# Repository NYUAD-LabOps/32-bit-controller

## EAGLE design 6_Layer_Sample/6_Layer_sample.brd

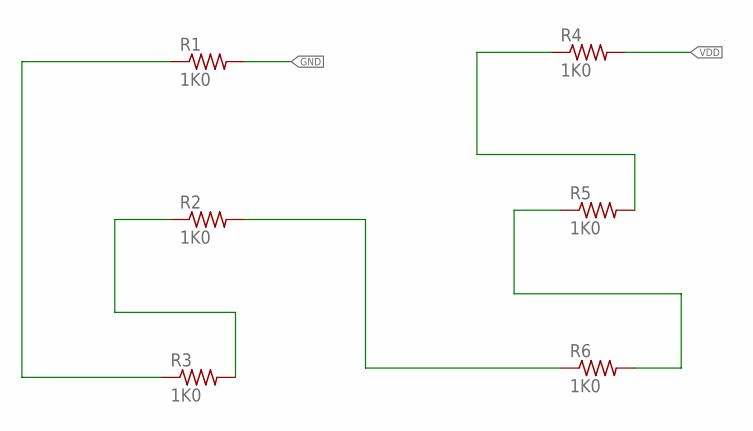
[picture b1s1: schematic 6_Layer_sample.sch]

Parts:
R1, R2, R3, R4, R5, R6: 1K0; 0402

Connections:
GND: R1.P$2 (2)
unnamed: R1.P$1 (1), R3.P$1 (1)
unnamed: R2.P$1 (1), R3.P$2 (2)
unnamed: R2.P$2 (2), R6.P$1 (1)
unnamed: R5.P$1 (1), R6.P$2 (2)
unnamed: R4.P$1 (1), R5.P$2 (2)
VDD: R4.P$2 (2)

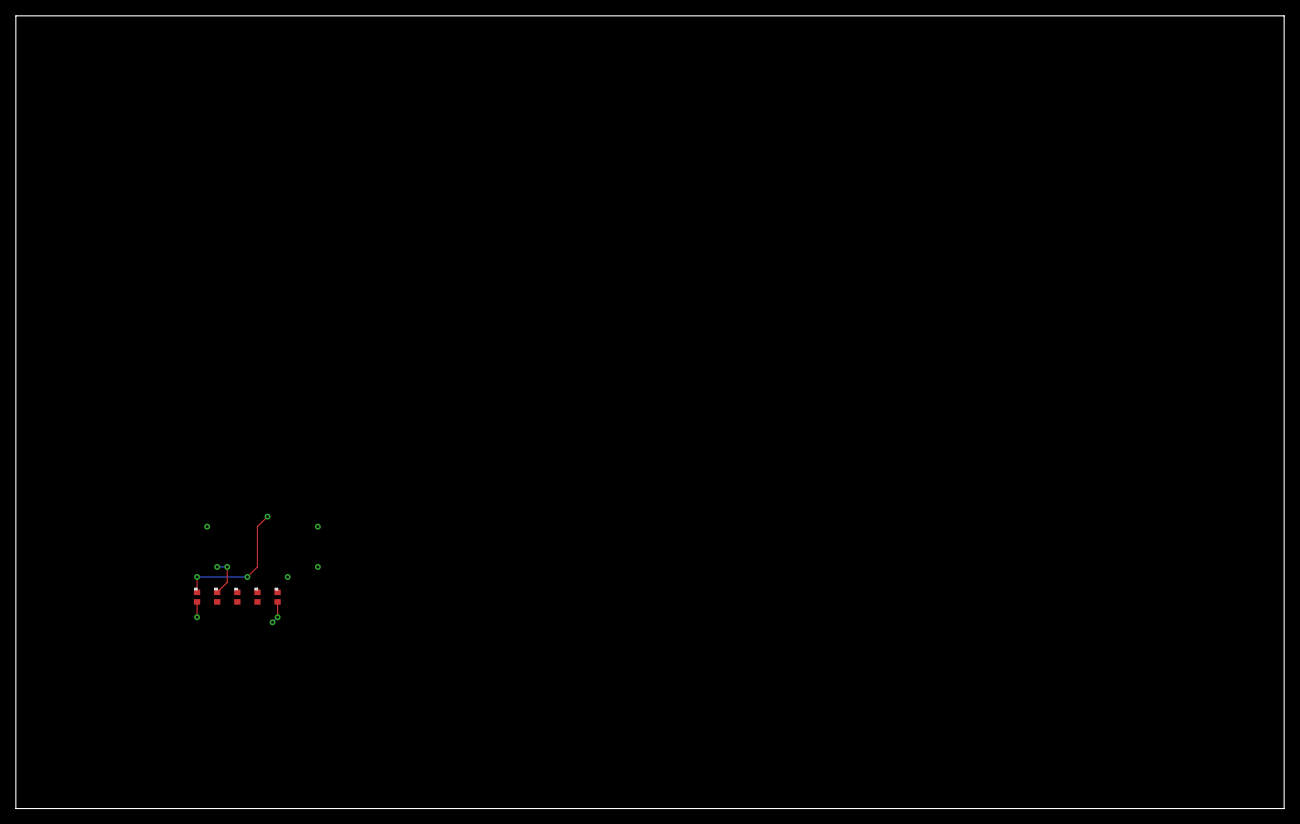
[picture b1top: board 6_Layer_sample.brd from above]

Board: 6 copper layers, 160.0 x 100.0 mm, 6 parts (1 on the bottom side), 5 nets.

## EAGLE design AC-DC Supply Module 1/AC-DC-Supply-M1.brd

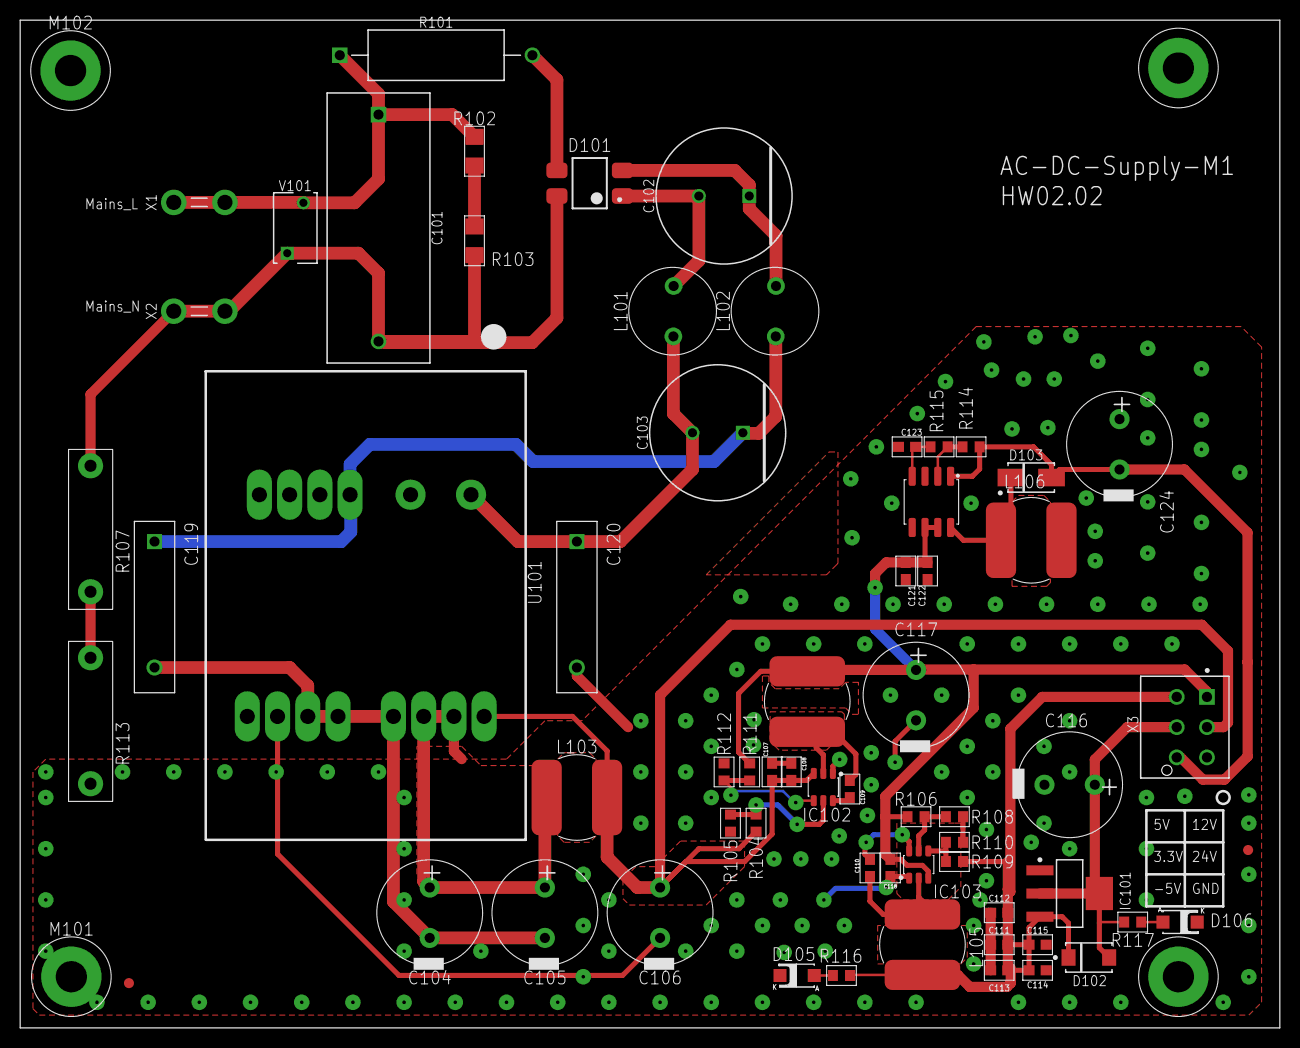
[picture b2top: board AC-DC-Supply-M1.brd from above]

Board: 2 copper layers, 125.0 x 100.0 mm, 67 parts (0 on the bottom side), 29 nets.

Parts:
C101: R49AN347050B1M
C102, C103: 860011378008; RADIAL_D13.0P5.0H25.0
C104, C105, C106, C116, C117, C124: 50PX470MEFC10X20; CAPACITOR-ELKO-RM5-10X16
C107, C109, C110, C115, C123: 100nF/50V; 0603
C108, C118, C121: 1uF/35V; 0603
C111, C112, C113, C114, C122: 10uF/25V; 0603
C119, C120: ERP610W471MEF0; CAP-P12.5-H15-W4-D1
D101: MB10S; SOIC4W
D102: STTH1L06ASTMICROELECTRONICS_STTH1L06A_0_0; SMA_STTH1L06A
D103: SS14; SMA
D105, D106: 26-21/GPC-F3138B/CA; SMD1206-LED
FID101, FID102: FIDUCIAL
IC101: LD1117S33TR; SOT223_LD1117S33TR
IC102, IC103: TPS54202DDCR; SOT23-6
IC104: MAX764CSA+; SOIC8
L101, L102: RLB0914-102KL; THTINDUCTOR8MM7
L103, L104, L105, L106: SRN8040TA-220M
M101, M102, M103, M104: M_HOLE_3M; PCB_SCREW_M3_POWER
R101: ERG-2SJ390V; ERG-2SJ390V_0
R102, R103: R_1206; R1206
R104: 1K 1%; R0603
R105: 10K; R0603
R106: 1K 1 %; R0603
R107, R113: RNF12FTD10M0; RES-RM12.5-VR37
R108, R115: 10k 1%; R0603
R109: 22K 1%; R0603
R110: 3k01 1%; R0603
R111: 100k 1%; R0603
R112: 4.3k 1%; R0603
R114: 33k 1%; R0603
R116: 162R 1%; R0603
R117: 82R 1%; R0603
U101: BPM2417SJ
V101: B72205S0271K101B72205S2131K101; EPCOS_B72205S0271K101_0
X1, X2: 726386-2; TE_726386-2_MODIFIED
X3: MOLEX_206832-0601MOLEX_206832-0601; MOLEX_206832-0601

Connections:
10_AC-DC_SUPPLY:N$1: IC102.4, R111.2, R112.2
10_AC-DC_SUPPLY:N$2: R102.1, R103.2
10_AC-DC_SUPPLY:N$3: R107.2, R113.1
10_AC-DC_SUPPLY:N$4: D101.3, R101.2
10_AC-DC_SUPPLY:N$5: C102.2, D101.1, L101.1
10_AC-DC_SUPPLY:N$6: C102.1, D101.2, L102.1
10_AC-DC_SUPPLY:N$7: C103.2, C120.P$1, L101.2, U101.1
10_AC-DC_SUPPLY:N$8: C103.1, C119.P$1, L102.2, U101.3
10_AC-DC_SUPPLY:N$9: C109.2, IC102.2, L104.1
10_AC-DC_SUPPLY:N$10: IC102.5, R104.1, R105.2
10_AC-DC_SUPPLY:N$11: C104.1, C105.1, L103.1, U101.12, U101.13
10_AC-DC_SUPPLY:N$12: C109.1, IC102.6
10_AC-DC_SUPPLY:N$13: C110.2, IC103.2, L105.1
10_AC-DC_SUPPLY:N$14: IC104.2, R114.1, R115.2
10_AC-DC_SUPPLY:N$15: IC103.4, R109.2, R110.1
10_AC-DC_SUPPLY:N$16: IC103.5, R106.1, R108.2
10_AC-DC_SUPPLY:N$17: D105.1, R116.2
10_AC-DC_SUPPLY:N$18: D103.1, IC104.8, L106.2
10_AC-DC_SUPPLY:N$19: D106.1, R117.2
10_AC-DC_SUPPLY:N$20: C123.1, IC104.4, R115.1
10_AC-DC_SUPPLY:N$21: C110.1, IC103.6
GND: C104.2, C105.2, C106.2, C107.2, C108.2, C111.1, C112.1, C113.1, C114.1, C115.2, C116.2, C117.2, C118.1, C119.P$2, C120.P$2, C121.1, C122.1, C123.2, C124.1, D105.2, D106.2, IC101.1, IC102.1, IC103.1, IC104.3, IC104.5, L106.1, M101.1, M104.1, R105.1, R108.1, R110.2, R112.1, R113.2, U101.08, U101.09, U101.10, U101.11, X3.5
unnamed: C101.1, R101.1, R102.2, V101.2, X1.1, X1.1-2
unnamed: C101.2, D101.4, R103.1, R107.1, V101.1, X2.1, X2.1-2
V_3V3: C116.1, D102.2, IC101.2, IC101.4, R117.1, X3.4
V_5V0: C111.2, C112.2, C113.2, C114.2, C115.1, D102.1, IC101.3, L105.2, R109.1, R116.1, X3.2
V_12V0: C117.1, C118.2, C121.2, C122.2, IC103.3, IC104.6, IC104.7, L104.2, R106.2, R111.1, X3.1
V_24V0: C106.1, C107.1, C108.1, IC102.3, L103.2, R104.2, U101.14, X3.3
V_-5V0: C124.2, D103.2, IC104.1, R114.2, X3.6

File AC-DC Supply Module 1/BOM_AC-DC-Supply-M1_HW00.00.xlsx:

Part | Value | Device | Package | DESCRIPTION | LIB_STATUS | MFN | MFR | OUR-STOCK | OUR_STOCK | PACKAGE2 | PART_VALUE | PRICE-1 | PRICE_1 | STOCK | SUPPLIER-1
C101 | R49AN347050B1M | R49AN347050B1M | R49AN347050B1M | Film,X1,470nF/330Vac,THT | Verified | R49AN347050B1M | Kemet |  | 8 |  | 470nF/330VAC | 1.51 |  |  | Digikey
C102 | 860011378008 | 860011378008 | RADIAL_D13.0P5.0H25.0 | Electrolytic Cap 33µF 400V 13mm Radial WCAP-ATG8 |  |  | 860011378008 |  |  | 4
C103 | 860011378008 | 860011378008 | RADIAL_D13.0P5.0H25.0 | Electrolytic Cap 33µF 400V 13mm Radial WCAP-ATG8 |  |  | 860011378008 |  |  | 4
C104 | 50PX470MEFC10X20 | 50PX470MEFC10X20 | CAPACITOR-ELKO-RM5-10X16 | 470uF ±20% 50V 10mm 20mm 5mm 2000Hrs @ 105℃ -55℃ ~ +105℃ | Prototype | 50PX470MEFC10X20 | Rubicon |  | 20 |  | 470uF/50V | 0.14000000000000001 |  |  | LCSC
C105 | 50PX470MEFC10X20 | 50PX470MEFC10X20 | CAPACITOR-ELKO-RM5-10X16 | 470uF ±20% 50V 10mm 20mm 5mm 2000Hrs @ 105℃ -55℃ ~ +105℃ | Prototype | 50PX470MEFC10X20 | Rubicon |  | 20 |  | 470uF/50V | 0.14000000000000001 |  |  | LCSC
C106 | 50PX470MEFC10X20 | 50PX470MEFC10X20 | CAPACITOR-ELKO-RM5-10X16 | 470uF ±20% 50V 10mm 20mm 5mm 2000Hrs @ 105℃ -55℃ ~ +105℃ | Prototype | 50PX470MEFC10X20 | Rubicon |  | 20 |  | 470uF/50V | 0.14000000000000001 |  |  | LCSC
C107 | 100nF/50V | C_0603 | 603 |  |  | Open Source
C108 | 1uF/35V | C_0603 | 603 |  |  | Open Source
C109 | 100nF/50V | C_0603 | 603 |  |  | Open Source
C110 | 100nF/50V | C_0603 | 603 |  |  | Open Source
C111 | 10uF/25V | C_0603 | 603 |  |  | Open Source
C112 | 10uF/25V | C_0603 | 603 |  |  | Open Source
C113 | 10uF/25V | C_0603 | 603 |  |  | Open Source
C114 | 10uF/25V | C_0603 | 603 |  |  | Open Source
C115 | 100nF/50V | C_0603 | 603 |  |  | Open Source
C116 | 50PX470MEFC10X20 | 50PX470MEFC10X20 | CAPACITOR-ELKO-RM5-10X16 | 470uF ±20% 50V 10mm 20mm 5mm 2000Hrs @ 105℃ -55℃ ~ +105℃ | Prototype | 50PX470MEFC10X20 | Rubicon |  | 20 |  | 470uF/50V | 0.14000000000000001 |  |  | LCSC
C117 | 50PX470MEFC10X20 | 50PX470MEFC10X20 | CAPACITOR-ELKO-RM5-10X16 | 470uF ±20% 50V 10mm 20mm 5mm 2000Hrs @ 105℃ -55℃ ~ +105℃ | Prototype | 50PX470MEFC10X20 | Rubicon |  | 20 |  | 470uF/50V | 0.14000000000000001 |  |  | LCSC
C118 | 1uF/35V | C_0603 | 603 |  |  | Open Source
C119 | ERP610W471MEF0 | ERP610W471MEF0 | CAP-P12.5-H15-W4-D1 | 470 pF ±20% 760VAC Ceramic Capacitor Y5U (E) Radial X1,Y1 | Prototype | ERP610W471MEF0 | Kemet |  | 150 |  | 470pF/760VAC | 0.42 |  |  | Digikey
C120 | ERP610W471MEF0 | ERP610W471MEF0 | CAP-P12.5-H15-W4-D1 | 470 pF ±20% 760VAC Ceramic Capacitor Y5U (E) Radial X1,Y1 | Prototype | ERP610W471MEF0 | Kemet |  | 150 |  | 470pF/760VAC | 0.42 |  |  | Digikey
D101 | MB10S | MB10S | SOIC4W | 0.5 A 1000 V Low Leakage SMT Bridge Rectifier - SOIC-4 | Prototype | MB10S | On Semi, Diodes,MDD |  |  |  | Bridge Rectifier | 0.02 |  | 10 | Digikey
D102 | STTH1L06ASTMICROELECTRONICS_STTH1L06A_0_0 | STTH1L06ASTMICROELECTRONICS_STTH1L06A_0_0 | SMA_STTH1L06A |  |  |  |  |  |  | SMA
D105 | 26-21/GPC-F3138B/CA | 26-21/GPC-F3138B/CA | SMD1206-LED | Green SMD LED 1206, 160mcd | Prototype | 26-21/GPC-F3138B/CA | Everlight |  | 50 |  | Green LED | 0.06 |  |  | LCSC
D106 | 26-21/GPC-F3138B/CA | 26-21/GPC-F3138B/CA | SMD1206-LED | Green SMD LED 1206, 160mcd | Prototype | 26-21/GPC-F3138B/CA | Everlight |  | 50 |  | Green LED | 0.06 |  |  | LCSC
FID101 | FIDUCIAL | FIDUCIAL | FIDUCIAL
FID102 | FIDUCIAL | FIDUCIAL | FIDUCIAL
IC101 | LD1117S33TR | LD1117S33TR | SOT223_LD1117S33TR | LDO,Fixed 15V 3.3V 1.3V @ 800mA SOT-223 | Verified | LD1117S33TR | STmicro, Diodes, TI, |  | 10 |  | xx1117x33xx |  | 7.0000000000000007E-2 |  | LCSC
IC102 | AP63301WU-7 | AP63301WU-7 | SOT23-6 | Buck 3.8V to 32V Input 3A Low IQ Synchronous Buck Converter with Enhanced EMI | Verified |  | Diodes |  | 10 |  | AP63301WU-7 | 0.25 |  |  | Digikey
IC103 | AP63301WU-7 | AP63301WU-7 | SOT23-6 | Buck 3.8V to 32V Input 3A Low IQ Synchronous Buck Converter with Enhanced EMI | Verified |  | Diodes |  | 10 |  | AP63301WU-7 | 0.25 |  |  | Digikey
L101 | RLB0914-102KL | RLB0914-102KL | THTINDUCTOR8MM7 | Inductor Power Wirewound 1mH 10% 252KHz 40Q-Factor Ferrite 300mA 2.1Ohm | Prototype | RLB0914-102KL | Bourns |  | 0 |  | 1mH | 0.42 |  |  | Digikey
L102 | RLB0914-102KL | RLB0914-102KL | THTINDUCTOR8MM7 | Inductor Power Wirewound 1mH 10% 252KHz 40Q-Factor Ferrite 300mA 2.1Ohm | Prototype | RLB0914-102KL | Bourns |  | 0 |  | 1mH | 0.42 |  |  | Digikey
L103 | SRN8040TA-220M | SRN8040TA-220M | SRN8040TA-220M | FIXED IND 22UH 2.9A SMD, 73m-Ohm, Bourns | Verified | SRN8040TA-220M | Bourns |  | 10 |  | 22uH/2.9A |  |  |  | Digikey
L104 | SRN8040TA-220M | SRN8040TA-220M | SRN8040TA-220M | FIXED IND 22UH 2.9A SMD, 73m-Ohm, Bourns | Verified | SRN8040TA-220M | Bourns |  | 10 |  | 22uH/2.9A |  |  |  | Digikey
L105 | SRN8040TA-220M | SRN8040TA-220M | SRN8040TA-220M | FIXED IND 22UH 2.9A SMD, 73m-Ohm, Bourns | Verified | SRN8040TA-220M | Bourns |  | 10 |  | 22uH/2.9A |  |  |  | Digikey
M101 | M_HOLE_3M | M_HOLE_3M | PCB_SCREW_M3_POWER
M102 | M_HOLE_3M | M_HOLE_3M | PCB_SCREW_M3_POWER
M103 | M_HOLE_3M | M_HOLE_3M | PCB_SCREW_M3_POWER
M104 | M_HOLE_3M | M_HOLE_3M | PCB_SCREW_M3_POWER
R101 | ERG-2SJ390V | ERG-2SJ390V | ERG-2SJ390V_0
R102 | R_1206 | R_1206 | R1206 |  | Verified | CRCW1206220KJNEAHP | Vishay |  |  |  | 220K 5%
R103 | R_1206 | R_1206 | R1206 |  | Verified | CRCW1206220KJNEAHP | Vishay |  |  |  | 220K 5%
R104 |  | R_0603 | R0603 |  |  | Open Source
R105 |  | R_0603 | R0603 |  |  | Open Source
R106 |  | R_0603 | R0603 |  |  | Open Source
R107 | RNF12FTD10M0 | RNF12FTD10M0 | RES-RM12.5-VR37 | 10 MOhms ±1% 0.5W, 1/2W Through Hole Resistor Axial Flame Retardant Coating, Sa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 | Prototype | RNF12FTD10M0 | Stackpole Electronics Inc | 20 |  |  | 10Meg 5% | 0.28999999999999998 |  |  | Digikey
R108 |  | R_0603 | R0603 |  |  | Open Source
R109 | 15.8K 1% | R_0603 | R0603 |  |  | Open Source
R110 | 3k01 1% | R_0603 | R0603 |  |  | Open Source
R111 | 47k 1% | R_0603 | R0603 |  |  | Open Source
R112 | 3.3k 1% | R_0603 | R0603 |  |  | Open Source
R113 | RNF12FTD10M0 | RNF12FTD10M0 | RES-RM12.5-VR37 | 10 MOhms ±1% 0.5W, 1/2W Through Hole Resistor Axial Flame Retardant Coating, Sa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 | Prototype | RNF12FTD10M0 | Stackpole Electronics Inc | 20 |  |  | 10Meg 5% | 0.28999999999999998 |  |  | Digikey
R116 | 162R 1% | R_0603 | R0603 |  |  | Open Source
R117 | 82R 1% | R_0603 | R0603 |  |  | Open Source
U101 | BPM2417SJ | BPM2417SJ | BPM2417SJ | Ac/Dc Power Supply Module | Prototype | BPM2417SJ | Tamura |  | 5 |  | Power Sources | 7 |  |  | Digikey
V101 | B72205S0271K101B72205S2131K101 | B72205S0271K101B72205S2131K101 | EPCOS_B72205S0271K101_0 |  | Verified | B72205S0271K1011 | EPCOS |  | 10 |  | 430V, 400A | 0.31 |  |  | Digikey
X1 | 726386-2 | 726386-2 | TE_726386-2_MODIFIED | 0.250 (6.35mm) Quick Connect Male - Solder Connector Non-Insulated" |  | 726386-2 | TE Connectivity |  |  |  | 6.35mmx8mm | 0.24 |  |  | Digikey
X2 | 726386-2 | 726386-2 | TE_726386-2_MODIFIED | 0.250 (6.35mm) Quick Connect Male - Solder Connector Non-Insulated" |  | 726386-2 | TE Connectivity |  |  |  | 6.35mmx8mm | 0.24 |  |  | Digikey
X3 | MOLEX_206832-0601MOLEX_206832-0601 | MOLEX_206832-0601MOLEX_206832-0601 | MOLEX_206832-0601 | Connector Header Through Hole 6 position 3mm Microfit | Prototype | 206832-0601 | Molex |  | 20 |  | 6CCT x 2Row | 1.32 |  |  | Digikey

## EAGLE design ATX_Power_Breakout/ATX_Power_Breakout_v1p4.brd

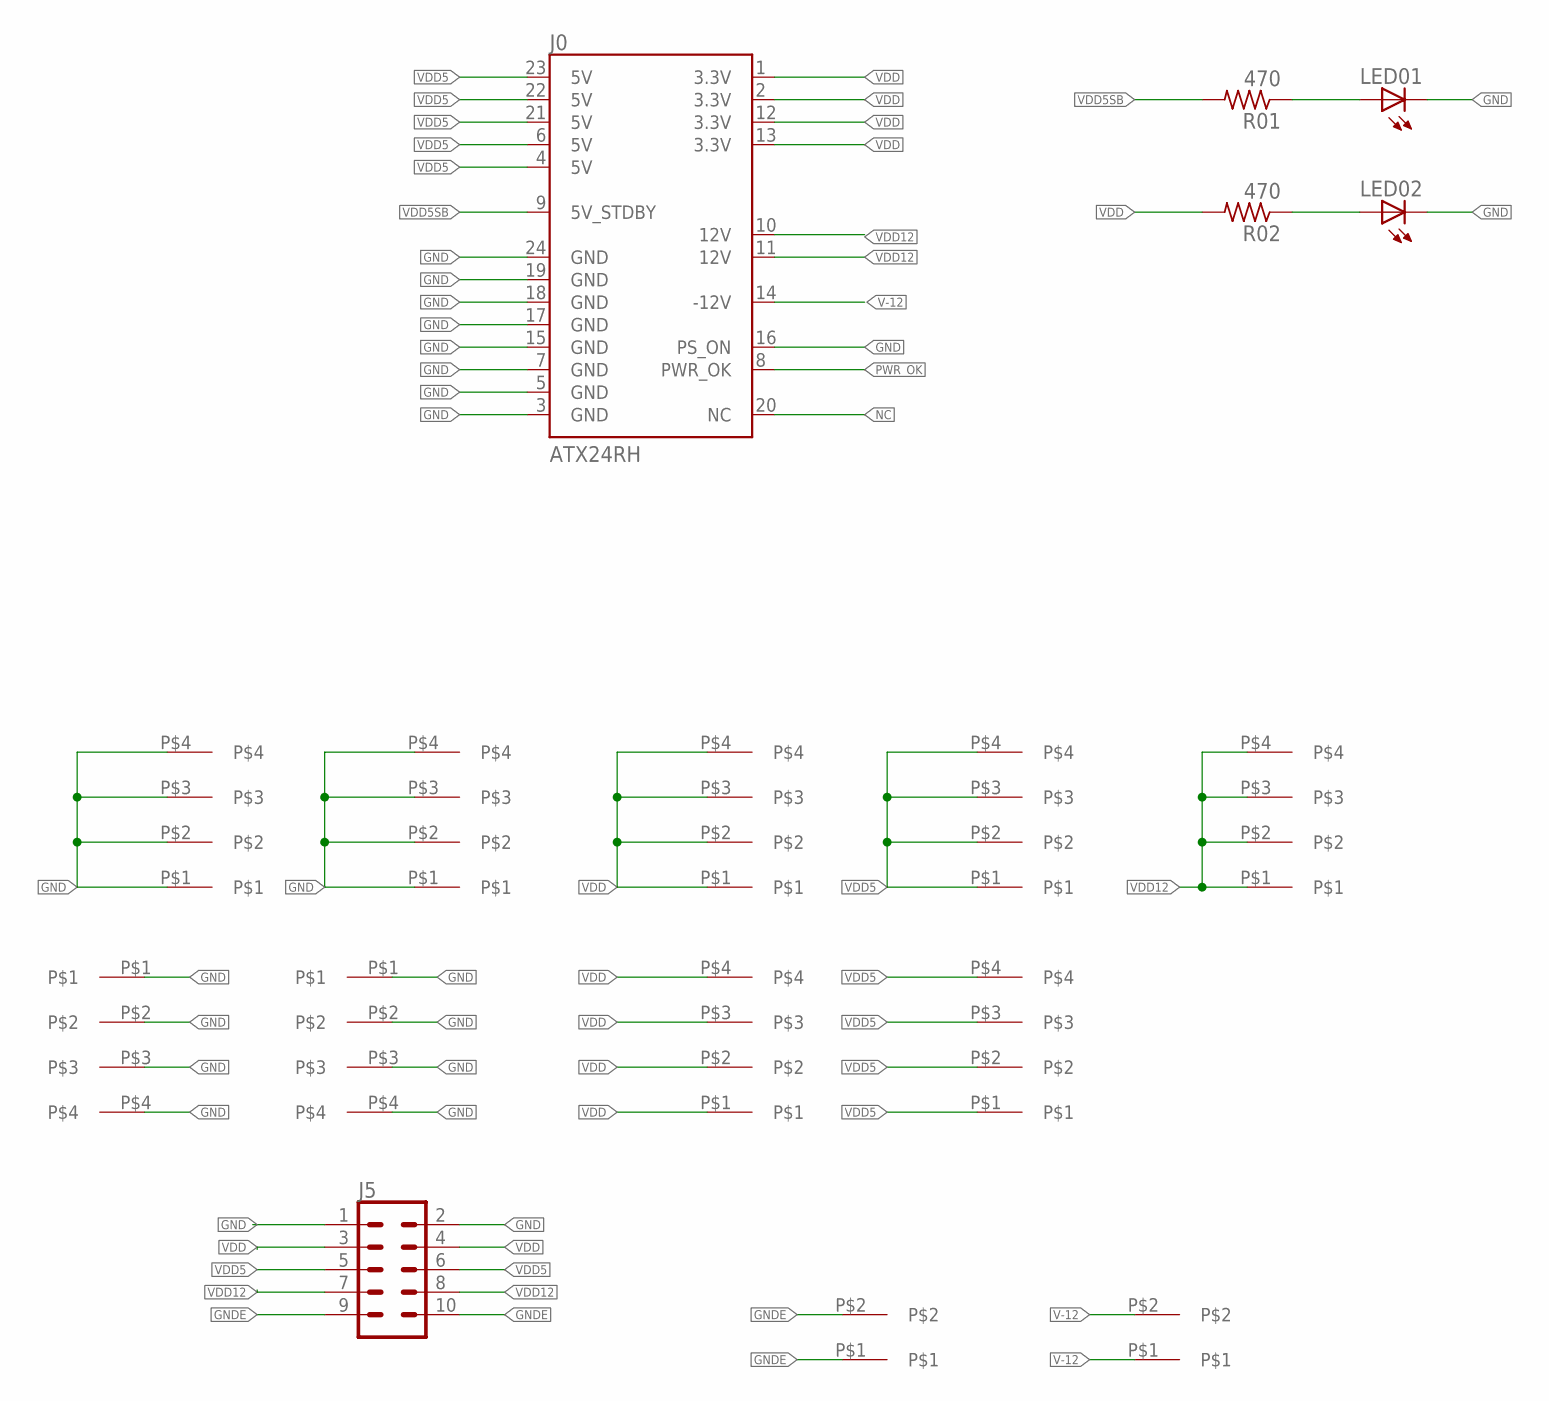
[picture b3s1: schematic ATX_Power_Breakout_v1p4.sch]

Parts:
J0: ATX24RH; ATX24_RIGHT_ANGLE
J1, J2, J3, J4, J7, J8, J9, J10, J12: 3.81MM_1_X_4_RT_ANGLE_PLUG_HEADER; 1X4_3.81MM_PITCH
J5: CONN_05X2PTH; 2X5
J6, J11: 3.81MM_1_X_2_RT_ANGLE_PLUG_HEADER; 2_3.81MM_PITCH
LED01, LED02: GREEN; LED_0805_GREEN
R01, R02: 470; 0402

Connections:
GND: J0.3 (GND), J0.5 (GND), J0.7 (GND), J0.15 (GND), J0.16 (PS_ON), J0.17 (GND), J0.18 (GND), J0.19 (GND), J0.24 (GND), J1.P$1, J1.P$2, J1.P$3, J1.P$4, J2.P$1, J2.P$2, J2.P$3, J2.P$4, J3.P$1, J3.P$2, J3.P$3, J3.P$4, J4.P$1, J4.P$2, J4.P$3, J4.P$4, J5.1, J5.2, LED01.C, LED02.C
GNDE: J5.9, J5.10, J6.P$1, J6.P$2
unnamed: LED01.A, R01.P$1 (1)
unnamed: LED02.A, R02.P$1 (1)
NC: J0.20 (NC)
PWR_OK: J0.8 (PWR_OK)
V-12: J0.14 (-12V), J11.P$1, J11.P$2
VDD: J0.1 (3.3V), J0.2 (3.3V), J0.12 (3.3V), J0.13 (3.3V), J5.3, J5.4, J7.P$1, J7.P$2, J7.P$3, J7.P$4, J8.P$1, J8.P$2, J8.P$3, J8.P$4, R02.P$2 (2)
VDD5: J0.4 (5V), J0.6 (5V), J0.21 (5V), J0.22 (5V), J0.23 (5V), J5.5, J5.6, J9.P$1, J9.P$2, J9.P$3, J9.P$4, J10.P$1, J10.P$2, J10.P$3, J10.P$4
VDD5SB: J0.9 (5V_STDBY), R01.P$2 (2)
VDD12: J0.10 (12V), J0.11 (12V), J5.7, J5.8, J12.P$1, J12.P$2, J12.P$3, J12.P$4

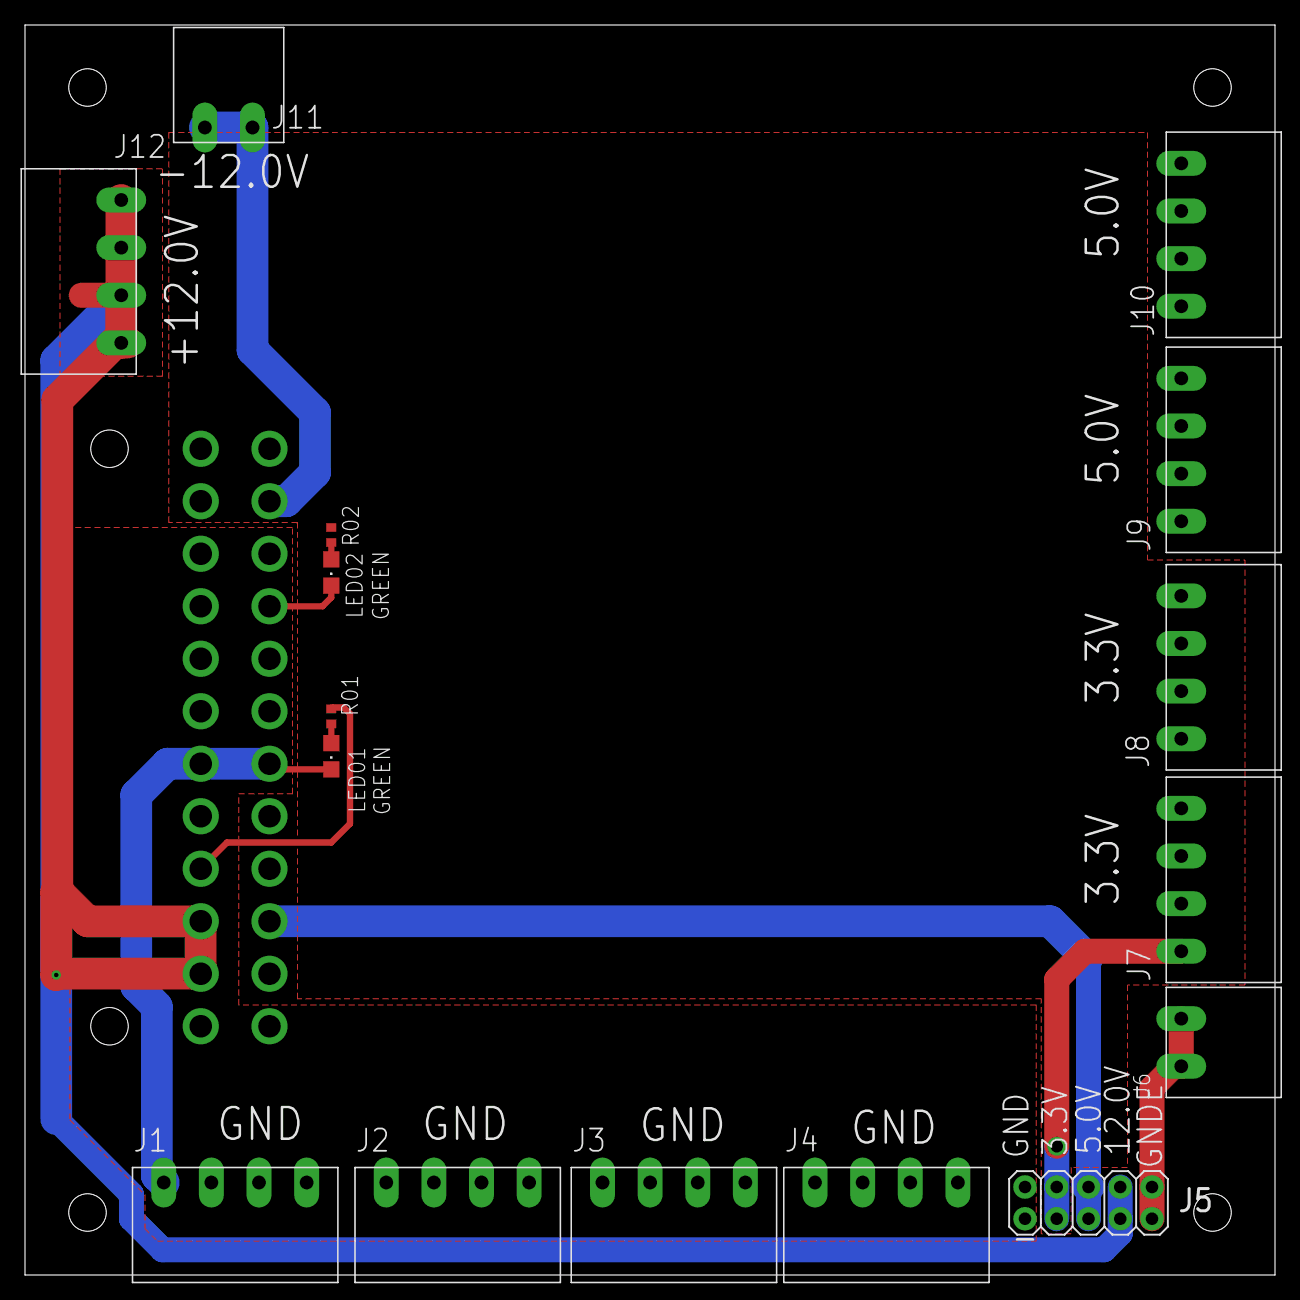
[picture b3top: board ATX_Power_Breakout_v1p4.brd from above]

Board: 2 copper layers, 100.0 x 100.0 mm, 17 parts (1 on the bottom side), 9 nets.
